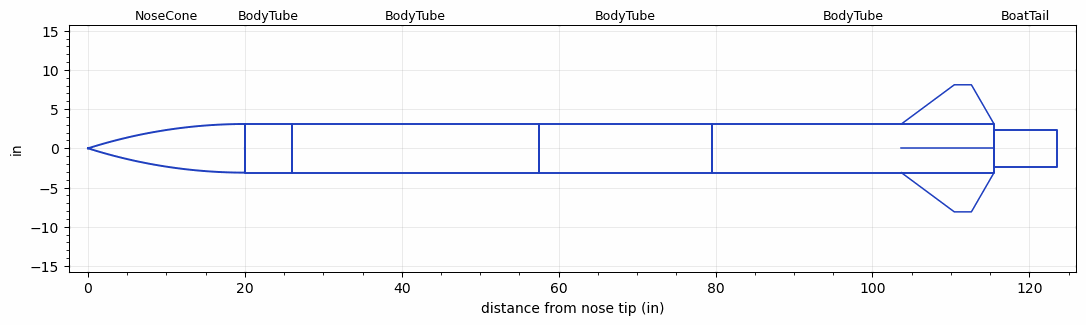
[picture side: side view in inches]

<RASAeroDocument>
 <FileVersion>2</FileVersion>
 <RocketDesign>
  <NoseCone>
   <Length>20</Length>
   <Diameter>6.2</Diameter>
   <Shape>Tangent Ogive</Shape>
   <Location>0</Location>
  </NoseCone>
  <BodyTube>
   <Length>6</Length>
   <Diameter>6.2</Diameter>
   <Location>20</Location>
  </BodyTube>
  <BodyTube>
   <Length>31.4999</Length>
   <Diameter>6.2</Diameter>
   <Location>25.9999</Location>
  </BodyTube>
  <BodyTube>
   <Length>22</Length>
   <Diameter>6.2</Diameter>
   <RailGuideDiameter>0.62</RailGuideDiameter>
   <RailGuideHeight>0.4495</RailGuideHeight>
   <Location>57.4999</Location>
  </BodyTube>
  <BodyTube>
   <Length>35.9999</Length>
   <Diameter>6.2</Diameter>
   <RailGuideDiameter>0.62</RailGuideDiameter>
   <RailGuideHeight>0.4495</RailGuideHeight>
   <Location>79.4998</Location>
   <Fin>
    <Count>4</Count>
    <Chord>11.811</Chord>
    <Span>5</Span>
    <SweepDistance>6.748</SweepDistance>
    <TipChord>2.1772</TipChord>
    <Thickness>0.1875</Thickness>
    <Location>11.811</Location>
    <AirfoilSection>Rounded</AirfoilSection>
   </Fin>
  </BodyTube>
  <BoatTail>
   <Length>8</Length>
   <Diameter>4.75</Diameter>
   <RearDiameter>4.75</RearDiameter>
   <Location>115.4998</Location>
  </BoatTail>
  <Surface>Smooth (Zero Roughness)</Surface>
  <CD>0</CD>
  <ModifiedBarrowman>False</ModifiedBarrowman>
  <Turbulence>False</Turbulence>
  <UseBooster1>False</UseBooster1>
  <UseBooster2>False</UseBooster2>
 </RocketDesign>
 <LaunchSite>
  <Altitude>2930.0001</Altitude>
  <Pressure>27.0263</Pressure>
  <RodAngle>6</RodAngle>
  <RodLength>148.4997</RodLength>
  <Temperature>120</Temperature>
  <WindSpeed>15</WindSpeed>
 </LaunchSite>
 <Recovery>
  <Altitude1>1312.336</Altitude1>
  <Altitude2>0</Altitude2>
  <DeviceType1>Parachute</DeviceType1>
  <DeviceType2>None</DeviceType2>
  <Event1>True</Event1>
  <Event2>False</Event2>
  <Size1>95.9998</Size1>
  <Size2>0</Size2>
  <EventType1>Altitude</EventType1>
  <EventType2>None</EventType2>
  <CD1>2.2</CD1>
  <CD2>0</CD2>
 </Recovery>
 <SimulationList>
  <Simulation>
   <SustainerLaunchWt>72.607</SustainerLaunchWt>
   <SustainerCG>67.1063</SustainerCG>
   <SustainerIgnitionDelay>0</SustainerIgnitionDelay>
   <Booster1SeparationDelay>0</Booster1SeparationDelay>
   <Booster1IgnitionDelay>0</Booster1IgnitionDelay>
   <IncludeBooster1>False</IncludeBooster1>
   <Booster2Delay>0</Booster2Delay>
   <IncludeBooster2>False</IncludeBooster2>
  </Simulation>
  <Simulation>
   <SustainerLaunchWt>72.607</SustainerLaunchWt>
   <SustainerCG>67.1063</SustainerCG>
   <SustainerIgnitionDelay>0</SustainerIgnitionDelay>
   <Booster1SeparationDelay>0</Booster1SeparationDelay>
   <Booster1IgnitionDelay>0</Booster1IgnitionDelay>
   <IncludeBooster1>False</IncludeBooster1>
   <Booster2Delay>0</Booster2Delay>
   <IncludeBooster2>False</IncludeBooster2>
  </Simulation>
  <Simulation>
   <SustainerLaunchWt>72.607</SustainerLaunchWt>
   <SustainerCG>67.1063</SustainerCG>
   <SustainerIgnitionDelay>0</SustainerIgnitionDelay>
   <Booster1SeparationDelay>0</Booster1SeparationDelay>
   <Booster1IgnitionDelay>0</Booster1IgnitionDelay>
   <IncludeBooster1>False</IncludeBooster1>
   <Booster2Delay>0</Booster2Delay>
   <IncludeBooster2>False</IncludeBooster2>
  </Simulation>
  <Simulation>
   <SustainerLaunchWt>72.607</SustainerLaunchWt>
   <SustainerCG>67.1063</SustainerCG>
   <SustainerIgnitionDelay>0</SustainerIgnitionDelay>
   <Booster1SeparationDelay>0</Booster1SeparationDelay>
   <Booster1IgnitionDelay>0</Booster1IgnitionDelay>
   <IncludeBooster1>False</IncludeBooster1>
   <Booster2Delay>0</Booster2Delay>
   <IncludeBooster2>False</IncludeBooster2>
  </Simulation>
 </SimulationList>
</RASAeroDocument>
